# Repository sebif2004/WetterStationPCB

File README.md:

# WetterStationPCB
Weather station controller (Battery + Buck-Boost-converter + ESP32/s3)
4 Layer PCB ~10A Buck Boost 21700 Battery

My second PCB disigning project (stil untestet but in manufacturing)

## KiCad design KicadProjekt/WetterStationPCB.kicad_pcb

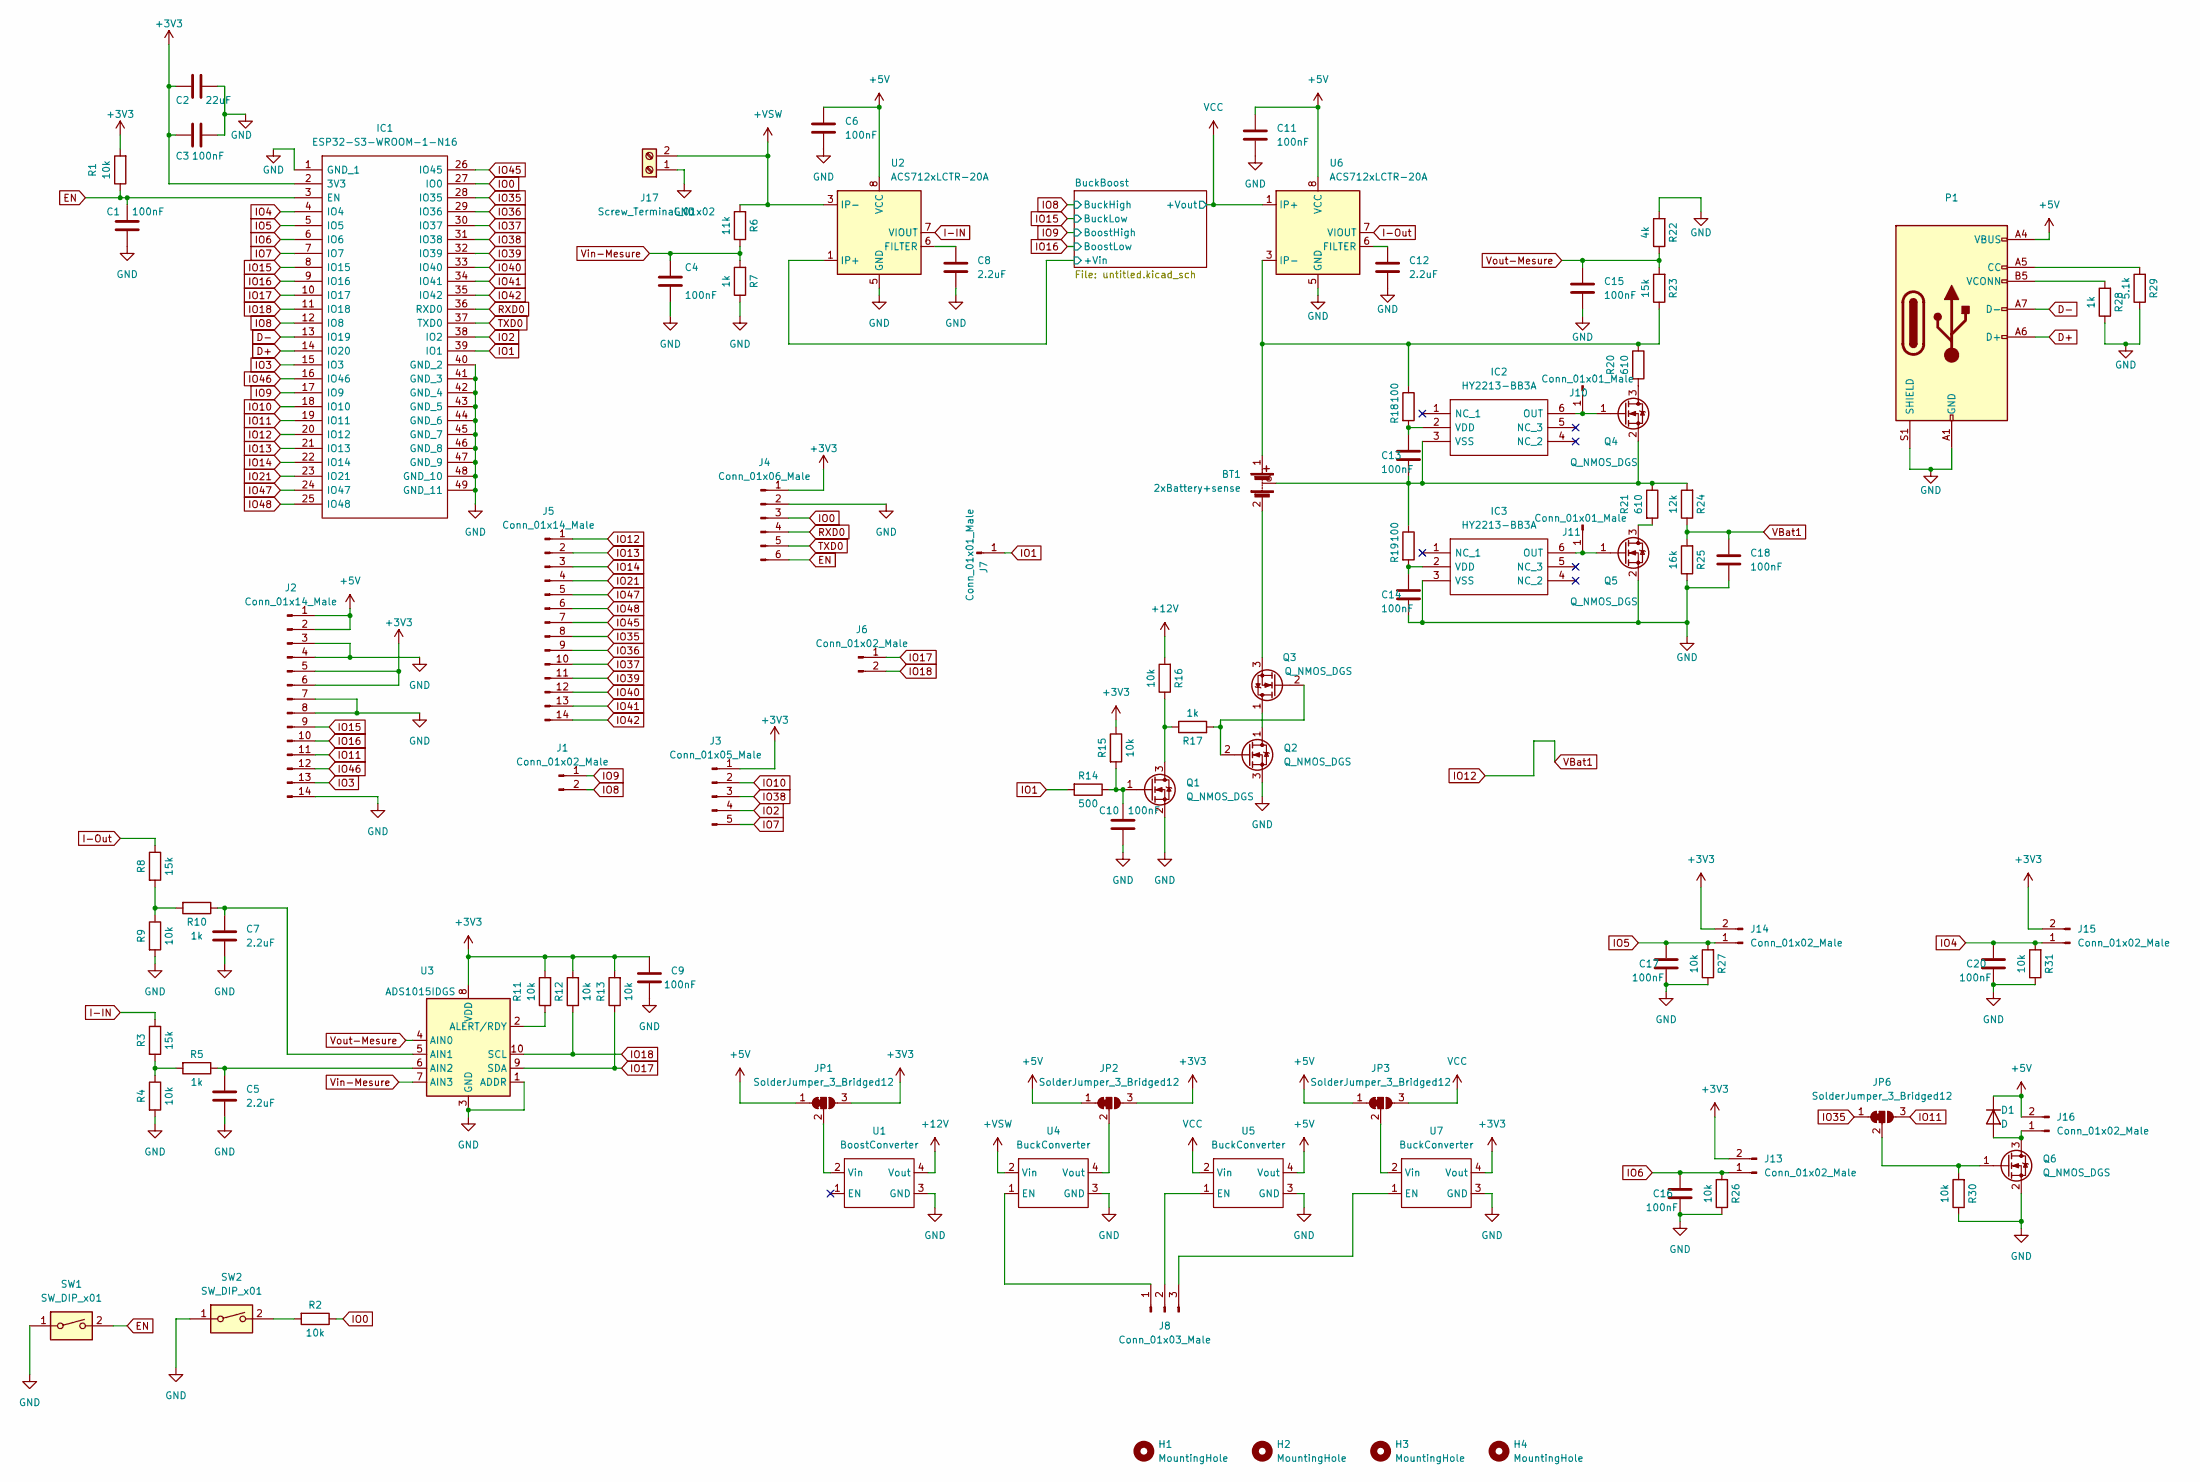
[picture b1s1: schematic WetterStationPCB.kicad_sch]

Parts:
BT1: 2xBattery+sense; 2x18650+21700-Holder
C1, C3, C4, C6, C9, C10, C11, C13, C14, C15, C16, C17, C18, C20: 100nF; C_0805_2012Metric_Pad1.18x1.45mm_HandSolder
C2: 22uF; C_1210_3225Metric_Pad1.33x2.70mm_HandSolder
C5, C7, C8, C12: 2.2uF; C_0805_2012Metric_Pad1.18x1.45mm_HandSolder
D1: D; D_SMA_Handsoldering
H1, H2, H3, H4: MountingHole; MountingHole_2.7mm_M2.5
IC1: ESP32-S3-WROOM-1-N16; ESP32S3WROOM1N16; Manufacturer_Part_Number ESP32-S3-WROOM-1-N16; Mouser Part Number 356-ESP32S3WROOM1N16
IC2, IC3: HY2213-BB3A; SOT95P280X140-6N; Manufacturer_Part_Number HY2213-BB3A
J1, J6: Conn_01x02_Male; PinSocket_1x02_P2.54mm_Vertical
J2, J5: Conn_01x14_Male; PinSocket_1x14_P2.54mm_Vertical
J3: Conn_01x05_Male; PinHeader_1x05_P2.54mm_Vertical
J4: Conn_01x06_Male; PinSocket_1x06_P2.54mm_Vertical
J7, J10, J11: Conn_01x01_Male; PinHeader_1x01_P2.54mm_Vertical
J8: Conn_01x03_Male; PinSocket_1x03_P2.54mm_Vertical
J13, J14, J15, J16: Conn_01x02_Male; PinHeader_1x02_P2.54mm_Vertical
J17: Screw_Terminal_01x02; TerminalBlock_bornier-2_P5.08mm
JP1, JP2, JP3: SolderJumper_3_Bridged12; SolderJumper-3_P2.0mm_Open_TrianglePad1.0x1.5mm
JP6: SolderJumper_3_Bridged12; SolderJumper-3_P1.3mm_Bridged12_Pad1.0x1.5mm
P1: USB_C_Plug_USB2.0; USB_C_Receptacle_Palconn_UTC16-G
Q1, Q4, Q5, Q6: Q_NMOS_DGS; SOT-23
Q2, Q3: Q_NMOS_DGS; DirectFET_MX
R1, R2, R4, R9, R11, R12, R13, R15, R26, R27, R30, R31: 10k; R_0603_1608Metric_Pad0.98x0.95mm_HandSolder
R3, R8, R23: 15k; R_0603_1608Metric_Pad0.98x0.95mm_HandSolder
R5, R7, R10, R17, R28: 1k; R_0603_1608Metric_Pad0.98x0.95mm_HandSolder
R6: 11k; R_0603_1608Metric_Pad0.98x0.95mm_HandSolder
R14: 500; R_0603_1608Metric_Pad0.98x0.95mm_HandSolder
R16: 10k; R_0805_2012Metric_Pad1.20x1.40mm_HandSolder
R18, R19: 100; R_0603_1608Metric_Pad0.98x0.95mm_HandSolder
R20, R21: 610; R_2512_6332Metric_Pad1.40x3.35mm_HandSolder
R22: 4k; R_0603_1608Metric_Pad0.98x0.95mm_HandSolder
R24: 12k; R_0603_1608Metric_Pad0.98x0.95mm_HandSolder
R25: 16k; R_0603_1608Metric_Pad0.98x0.95mm_HandSolder
R29: 5.1k; R_0603_1608Metric_Pad0.98x0.95mm_HandSolder
SW1, SW2: SW_DIP_x01; SW_SPST_B3U-1000P
U1: BoostConverter; PinHeader_1x04_P2.54mm_Vertical
U2, U6: ACS712xLCTR-20A; SOIC-8_3.9x4.9mm_P1.27mm
U3: ADS1015IDGS; TSSOP-10_3x3mm_P0.5mm
U4, U5, U7: BuckConverter; PinHeader_1x04_P2.54mm_Vertical

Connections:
+3V3: C2.1, C3.1, C9.1, IC1.2 (3V3), J2.5, J2.6, J3.1, J4.1, J13.2, J14.2, J15.2, JP1.3 (B), JP2.3 (B), R1.2, R11.2, R12.2, R13.2, R15.1, U3.8 (VDD), U7.4 (Vout); also elsewhere on the board
+5V: C6.1, C11.1, D1.1 (K), J2.1, J2.2, J16.2, JP1.1 (A), JP2.1 (A), JP3.1 (A), P1.A4 (VBUS), P1.A9 (VBUS), P1.B4 (VBUS), P1.B9 (VBUS), U2.8 (VCC), U5.4 (Vout), U6.8 (VCC)
+12V: R16.2, U1.4 (Vout); also elsewhere on the board
+VSW: J17.2, R6.2, U2.3 (IP-), U2.4 (IP-), U4.2 (Vin)
/BuckBoost/+Vin: U2.1 (IP+), U2.2 (IP+); also elsewhere on the board
D+: IC1.14 (IO20), P1.A6 (D+)
D-: IC1.13 (IO19), P1.A7 (D-)
EN: C1.2, IC1.3 (EN), J4.6, R1.1, SW1.2
GND: C1.1, C2.2, C3.2, C4.2, C5.2, C6.2, C7.2, C8.2, C9.2, C10.1, C11.2, C12.2, C14.2, C15.2, C16.2, C17.2, C18.2, C20.2, IC1.1 (GND_1), IC1.40 (GND_2), IC1.41 (GND_3), IC1.42 (GND_4), IC1.43 (GND_5), IC1.44 (GND_6), IC1.45 (GND_7), IC1.46 (GND_8), IC1.47 (GND_9), IC1.48 (GND_10), IC1.49 (GND_11), IC3.3 (VSS), J2.3, J2.4, J2.7, J2.8, J2.14, J4.2, J17.1, P1.A1 (GND), P1.A12 (GND), P1.B1 (GND), P1.B12 (GND), P1.S1 (SHIELD), Q1.2 (S), Q2.3 (S), Q5.2 (S), Q6.2 (S), R4.2, R7.1, R9.2, R22.2, R25.1, R26.1, R27.1, R28.1, R29.1, R30.1, R31.1, SW1.1, SW2.1, U1.3 (GND), U2.5 (GND), U3.1 (ADDR), U3.3 (GND), U4.3 (GND), U5.3 (GND), U6.5 (GND), U7.3 (GND); also elsewhere on the board
I-IN: R3.1, U2.7 (VIOUT)
I-Out: R8.1, U6.7 (VIOUT)
IO0: IC1.27 (IO0), J4.3, R2.1
IO1: IC1.39 (IO1), J7.1, R14.2
IO2: IC1.38 (IO2), J3.4
IO3: IC1.15 (IO3), J2.13
IO4: C20.1, IC1.4 (IO4), J15.1, R31.2
IO5: C17.1, IC1.5 (IO5), J14.1, R27.2
IO6: C16.1, IC1.6 (IO6), J13.1, R26.2
IO7: IC1.7 (IO7), J3.5
IO8: IC1.12 (IO8), J1.2; also elsewhere on the board
IO9: IC1.17 (IO9), J1.1; also elsewhere on the board
IO10: IC1.18 (IO10), J3.2
IO11: IC1.19 (IO11), J2.11, JP6.3 (B)
IO12: C18.1, IC1.20 (IO12), J5.1, R24.1, R25.2
IO13: IC1.21 (IO13), J5.2
IO14: IC1.22 (IO14), J5.3
IO15: IC1.8 (IO15), J2.9
IO16: IC1.9 (IO16), J2.10
IO17: IC1.10 (IO17), J6.1, R13.1, U3.9 (SDA)
IO18: IC1.11 (IO18), J6.2, R12.1, U3.10 (SCL)
IO21: IC1.23 (IO21), J5.4
IO35: IC1.28 (IO35), J5.8, JP6.1 (A)
IO36: IC1.29 (IO36), J5.9
IO37: IC1.30 (IO37), J5.10
IO38: IC1.31 (IO38), J3.3
IO39: IC1.32 (IO39), J5.11
IO40: IC1.33 (IO40), J5.12
IO41: IC1.34 (IO41), J5.13
IO42: IC1.35 (IO42), J5.14
IO45: IC1.26 (IO45), J5.7
IO46: IC1.16 (IO46), J2.12
IO47: IC1.24 (IO47), J5.5
IO48: IC1.25 (IO48), J5.6
unnamed: BT1.1 (+), R18.1, R20.1, R23.1, U6.3 (IP-), U6.4 (IP-)
unnamed: BT1.2 (-), Q3.3 (S)
unnamed: BT1.3 (Vsense), C13.2, IC2.3 (VSS), Q4.2 (S), R19.1, R21.1, R24.2
unnamed: C5.1, R5.1, U3.6 (AIN2)
unnamed: C7.1, R10.1, U3.5 (AIN1)
unnamed: C8.1, U2.6 (FILTER)
unnamed: C10.2, Q1.1 (G), R14.1, R15.2
unnamed: C12.1, U6.6 (FILTER)
unnamed: C13.1, IC2.2 (VDD), R18.2
unnamed: C14.1, IC3.2 (VDD), R19.2
unnamed: D1.2 (A), J16.1, Q6.3 (D)
unnamed: IC2.6 (OUT), J10.1, Q4.1 (G)
unnamed: IC3.6 (OUT), J11.1, Q5.1 (G)
unnamed: JP1.2 (C), U1.2 (Vin)
unnamed: JP2.2 (C), U4.4 (Vout)
unnamed: JP3.2 (C), U7.2 (Vin)
unnamed: JP6.2 (C), Q6.1 (G), R30.2
unnamed: P1.A5 (CC), R29.2
unnamed: P1.B5 (VCONN), R28.2
unnamed: Q1.3 (D), R16.1, R17.1
unnamed: Q2.1 (D), Q3.1 (D)
unnamed: Q2.2 (G), Q3.2 (G), R17.2
unnamed: Q4.3 (D), R20.2
unnamed: Q5.3 (D), R21.2
unnamed: R2.2, SW2.2
unnamed: R3.2, R4.1, R5.2
unnamed: R8.2, R9.1, R10.2
unnamed: R11.1, U3.2 (ALERT/RDY)
unnamed: J8.1, U4.1 (EN)
unnamed: J8.2, U5.1 (EN)
unnamed: J8.3, U7.1 (EN)
RXD0: IC1.36 (RXD0), J4.4
TXD0: IC1.37 (TXD0), J4.5
VCC: JP3.3 (B), U5.2 (Vin), U6.1 (IP+), U6.2 (IP+); also elsewhere on the board
Vin-Mesure: C4.1, R6.1, R7.2, U3.7 (AIN3)
Vout-Mesure: C15.1, R22.1, R23.2, U3.4 (AIN0)

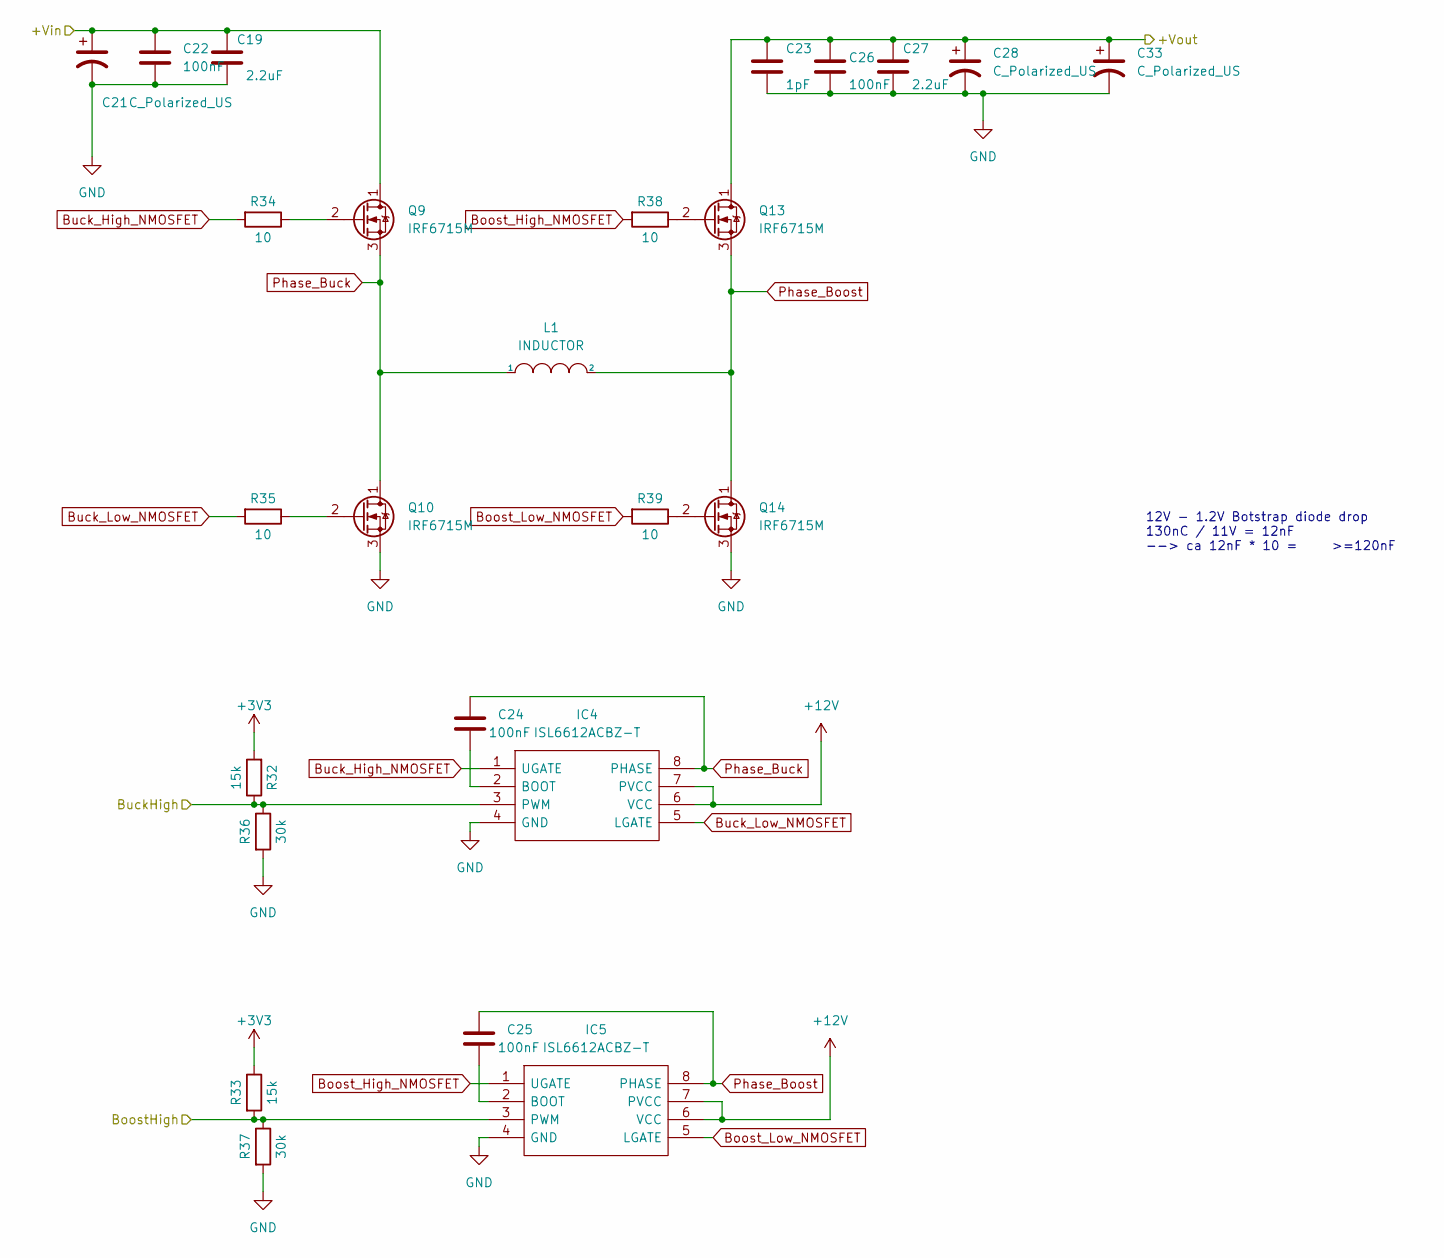
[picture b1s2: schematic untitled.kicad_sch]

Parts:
C19, C27: 2.2uF; C_0805_2012Metric_Pad1.18x1.45mm_HandSolder
C21, C28, C33: C_Polarized_US; CP_Radial_D10.0mm_P5.00mm
C22, C24, C25, C26: 100nF; C_0805_2012Metric_Pad1.18x1.45mm_HandSolder
C23: 1pF; C_0805_2012Metric_Pad1.18x1.45mm_HandSolder
IC4, IC5: ISL6612ACBZ-T; SOIC127P600X175-8N; Manufacturer_Part_Number ISL6612ACBZ-T; Mouser Part Number 968-ISL6612ACBZ-T
L1: INDUCTOR; Inductor-Universal-15x15
Q9, Q10, Q13, Q14: IRF6715M; DirectFET_MX
R32, R33: 15k; R_0603_1608Metric_Pad0.98x0.95mm_HandSolder
R34, R35, R38, R39: 10; R_0805_2012Metric_Pad1.20x1.40mm_HandSolder
R36, R37: 30k; R_0603_1608Metric_Pad0.98x0.95mm_HandSolder

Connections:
+3V3: R32.2, R33.1; also elsewhere on the board
+12V: IC4.6 (VCC), IC4.7 (PVCC), IC5.6 (VCC), IC5.7 (PVCC); also elsewhere on the board
/BuckBoost/+Vin: C19.1, C21.1, C22.1, Q9.1 (D); also elsewhere on the board
Boost_High_NMOSFET: IC5.1 (UGATE), R38.2
Boost_Low_NMOSFET: IC5.5 (LGATE), R39.2
Buck_High_NMOSFET: IC4.1 (UGATE), R34.2
Buck_Low_NMOSFET: IC4.5 (LGATE), R35.2
GND: C19.2, C21.2, C22.2, C23.2, C26.2, C27.2, C28.2, C33.2, IC4.4 (GND), IC5.4 (GND), Q10.3 (S), Q14.3 (S), R36.2, R37.2; also elsewhere on the board
IO8: IC4.3 (PWM), R32.1, R36.1; also elsewhere on the board
IO9: IC5.3 (PWM), R33.2, R37.1; also elsewhere on the board
unnamed: C24.2, IC4.2 (BOOT)
unnamed: C25.2, IC5.2 (BOOT)
unnamed: Q9.2 (G), R34.1
unnamed: Q10.2 (G), R35.1
unnamed: Q13.2 (G), R38.1
unnamed: Q14.2 (G), R39.1
Phase_Boost: C25.1, IC5.8 (PHASE), L1.2, Q13.3 (S), Q14.1 (D)
Phase_Buck: C24.1, IC4.8 (PHASE), L1.1, Q9.3 (S), Q10.1 (D)
VCC: C23.1, C26.1, C27.1, C28.1, C33.1, Q13.1 (D); also elsewhere on the board

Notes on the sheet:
12V - 1.2V Botstrap diode drop 130nC / 11V = 12nF --> ca 12nF * 10 = >=120nF

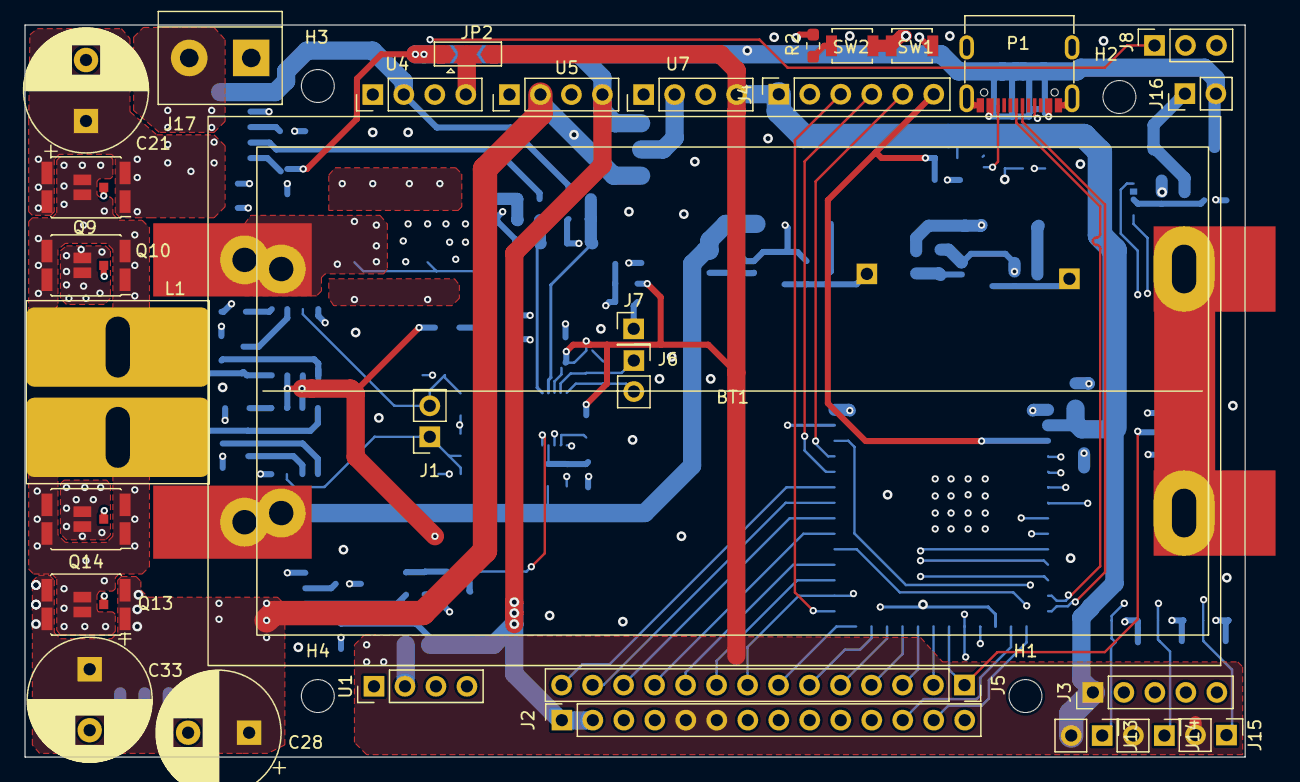
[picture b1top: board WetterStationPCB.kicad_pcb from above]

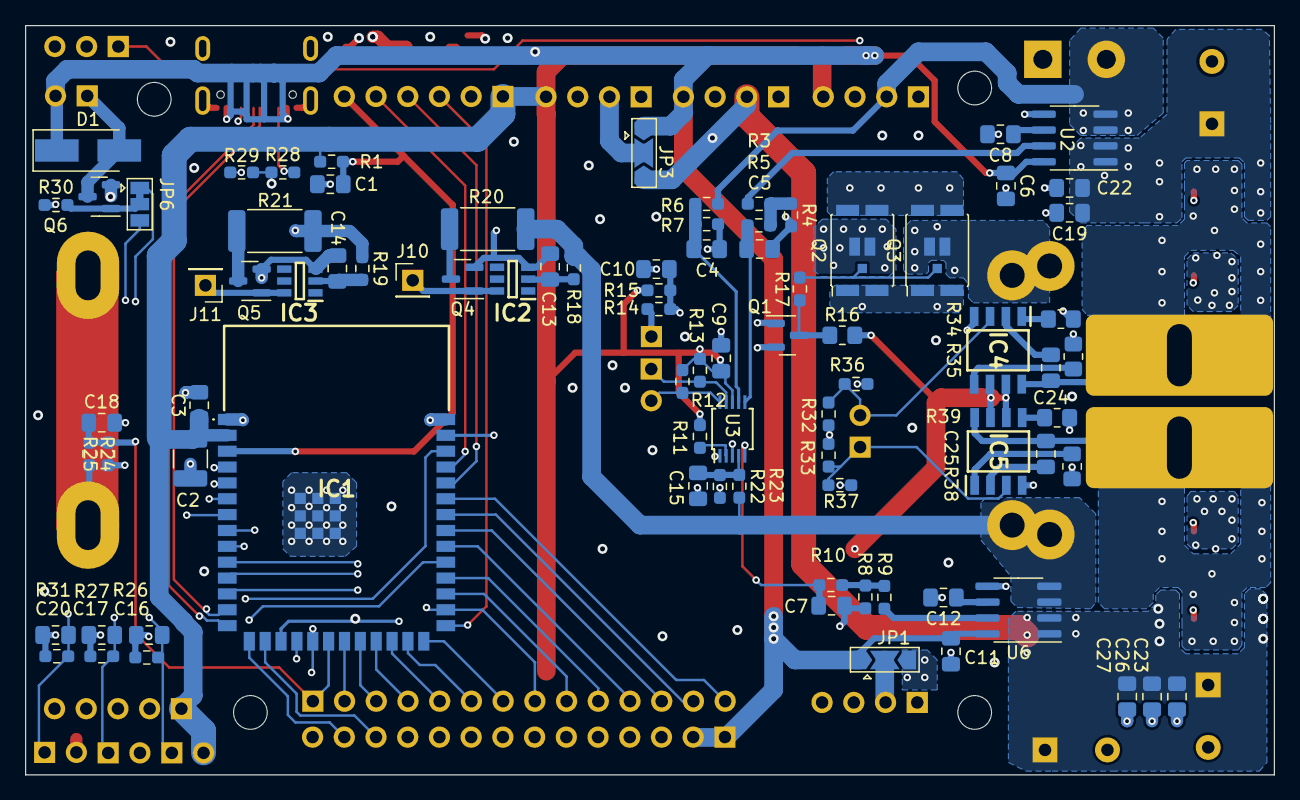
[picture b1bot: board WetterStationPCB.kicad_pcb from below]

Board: 4 copper layers, 100.0 x 60.0 mm, 119 parts (84 on the bottom side), 91 nets.

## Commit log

2022-09-29 Render Front + Back
